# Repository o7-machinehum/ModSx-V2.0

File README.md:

ModSx-V2.0
==========

The ModSx is open open source form factor for modular synths. 

V2.0 is a redesign of V1.0 - Instead of stacking like Arduino; the modules sit side by side.
This allows for more vertical mounted components, banana plugs, vert pots etc...

It is very much in it's infancy.

PWR Board / Proto Board
----------------
/PWR.JPG)
I've rolled the power and proto board into one, it now uses a standard ATX computer PSU and everything is fused properly.

-Walker / Ryan(DOT)CJW@Gmail(DOT)com

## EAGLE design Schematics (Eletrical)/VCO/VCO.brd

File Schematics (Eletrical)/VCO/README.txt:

__  __            _     _            _    _                 
 |  \/  |          | |   (_)          | |  | |                
 | \  / | __ _  ___| |__  _ _ __   ___| |__| |_   _ _ __ ___  
 | |\/| |/ _` |/ __| '_ \| | '_ \ / _ \  __  | | | | '_ ` _ \ 
 | |  | | (_| | (__| | | | | | | |  __/ |  | | |_| | | | | | |
 |_|  |_|\__,_|\___|_| |_|_|_| |_|\___|_|  |_|\__,_|_| |_| |_|
                                                              
V0.1 - Voltage Controlled Oscillator

Based off of a cct found on page 19 of TI's "LM13700" datasheet.

http://www.ti.com/lit/ds/symlink/lm13700.pdf

To do:

-Walker

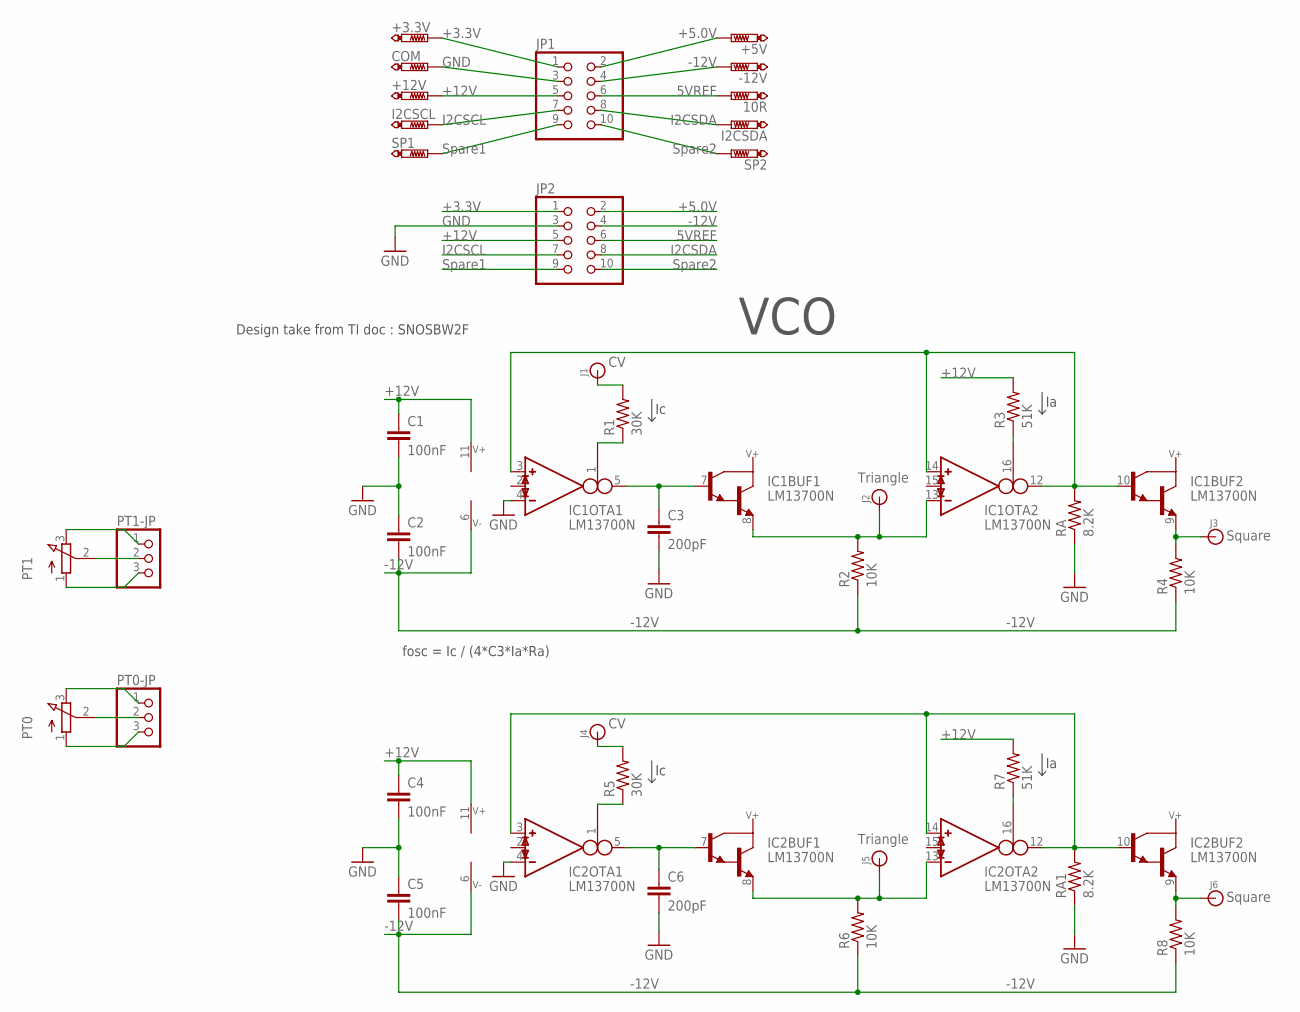
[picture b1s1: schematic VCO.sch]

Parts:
10R: PTR1B1,27; B1,27
+3.3V, +5V, +12V: PTR1B1,27; B1,27
-12V: PTR1B1,27; B1,27
C1, C2, C4, C5: 100nF; C5B2.5
C3, C6: 200pF; C5B2.5
COM: PTR1B1,27; B1,27
I2CSCL, I2CSDA: PTR1B1,27; B1,27
IC1, IC2: LM13700N; DIL16
J1, J2, J3, J4, J5, J6: BANANA_CONN
JP1, JP2: PINHD-2X5/90; 2X05/90
PT0, PT1: 3RP/1610N
PT0-JP, PT1-JP: PINHD-1X3; 1X03
R1, R5: 30K; 0207/10
R2, R4, R6, R8: 10K; 0207/10
R3, R7: 51K; 0207/10
RA, RA1: 8.2K; 0207/10
SP1, SP2: PTR1B1,27; B1,27

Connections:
5VREF: 10R.TP, JP1.6, JP2.6
+3.3V: +3.3V.TP, JP1.1, JP2.1
+5.0V: +5V.TP, JP1.2, JP2.2
+12V: +12V.TP, C1.1, C4.1, IC1.11 (V+), IC2.11 (V+), JP1.5, JP2.5, R3.2, R7.2
-12V: -12V.TP, C2.2, C5.2, IC1.6 (V-), IC2.6 (V-), JP1.4, JP2.4, R2.1, R4.1, R6.1, R8.1
CV: J1.P$1, R1.2
CV1: J4.P$1, R5.2
GND: C1.2, C2.1, C3.2, C4.2, C5.1, C6.2, COM.TP, IC1.4 (IN_N), IC2.4 (IN_N), JP1.3, JP2.3, RA.1, RA1.1
I2CSCL: I2CSCL.TP, JP1.7, JP2.7
I2CSDA: I2CSDA.TP, JP1.8, JP2.8
unnamed: C3.1, IC1.5 (OUT), IC1.7 (B)
unnamed: IC1.1 (I_BIAS), R1.1
unnamed: C6.1, IC2.5 (OUT), IC2.7 (B)
unnamed: IC1.16 (I_BIAS), R3.1
unnamed: IC2.1 (I_BIAS), R5.1
unnamed: IC1.3 (IN_P), IC1.10 (B), IC1.12 (OUT), IC1.14 (IN_P), RA.2
unnamed: IC2.3 (IN_P), IC2.10 (B), IC2.12 (OUT), IC2.14 (IN_P), RA1.2
unnamed: IC2.16 (I_BIAS), R7.1
unnamed: PT1.2 (S), PT1-JP.2
unnamed: PT1.3 (E), PT1-JP.1
unnamed: PT1.1 (A), PT1-JP.3
unnamed: PT0.2 (S), PT0-JP.2
unnamed: PT0.3 (E), PT0-JP.1
unnamed: PT0.1 (A), PT0-JP.3
SPARE1: JP1.9, JP2.9, SP1.TP
SPARE2: JP1.10, JP2.10, SP2.TP
SQ: IC1.9 (E), J3.P$1, R4.2
SQ1: IC2.9 (E), J6.P$1, R8.2
TRI: IC1.8 (E), IC1.13 (IN_N), J2.P$1, R2.2
TRI1: IC2.8 (E), IC2.13 (IN_N), J5.P$1, R6.2

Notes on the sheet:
+3.3V
GND
+12V
Spare1
+5.0V
-12V
5VREF
I2CSDA
I2CSCL
Spare2
Triangle
Square
Design take from TI doc : SNOSBW2F
VCO
fosc = Ic / (4*C3*Ia*Ra)

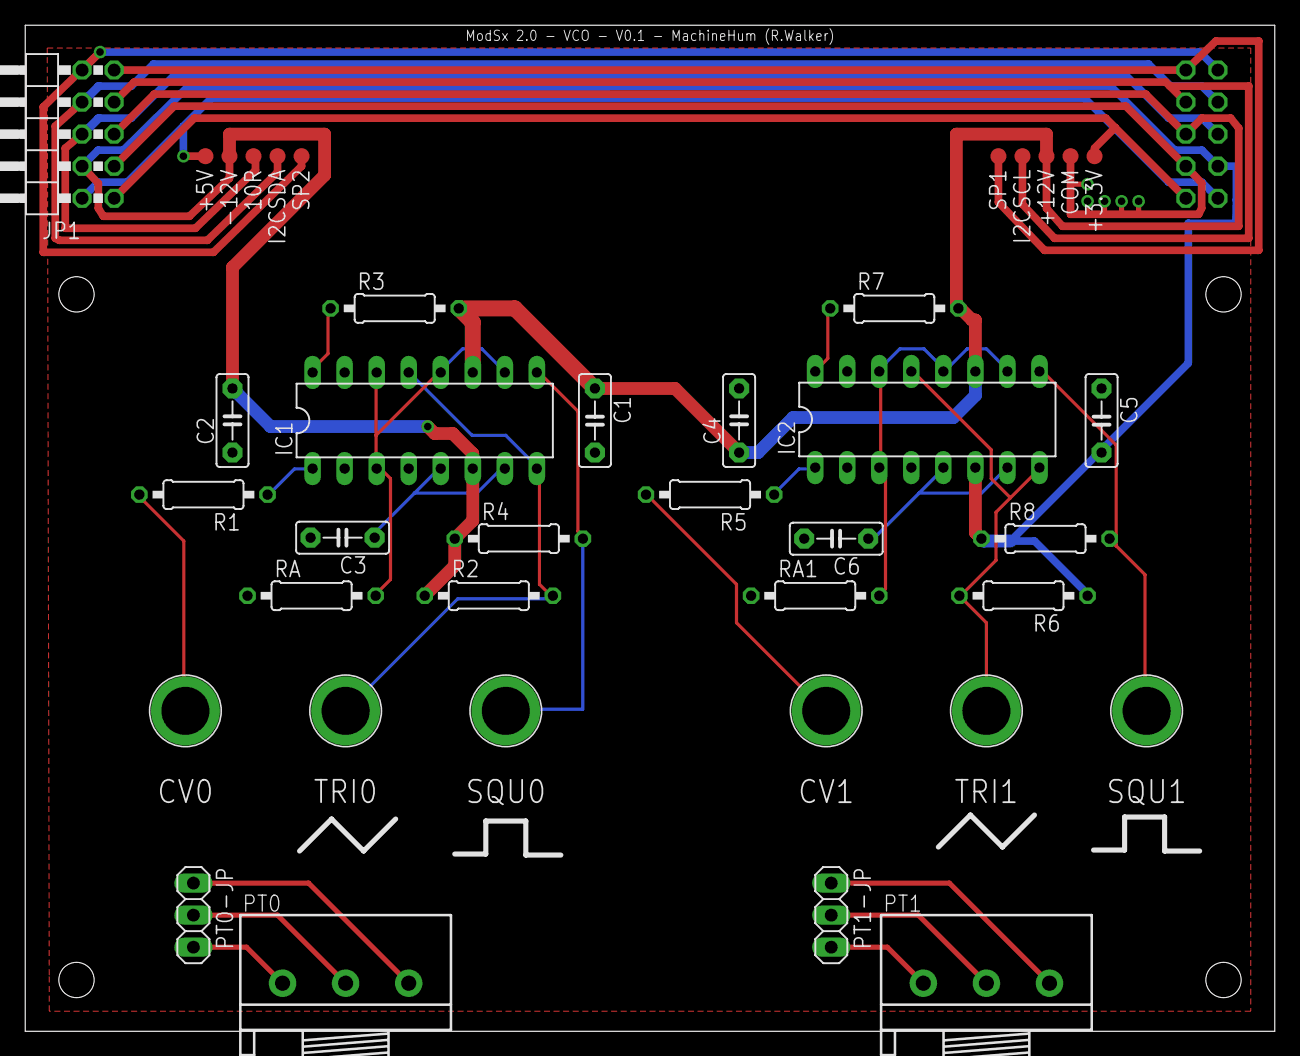
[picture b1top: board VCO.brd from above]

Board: 2 copper layers, 99.1 x 79.8 mm, 40 parts (1 on the bottom side), 30 nets.

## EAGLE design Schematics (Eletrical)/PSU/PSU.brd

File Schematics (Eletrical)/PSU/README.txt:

__  __            _     _            _    _                 
 |  \/  |          | |   (_)          | |  | |                
 | \  / | __ _  ___| |__  _ _ __   ___| |__| |_   _ _ __ ___  
 | |\/| |/ _` |/ __| '_ \| | '_ \ / _ \  __  | | | | '_ ` _ \ 
 | |  | | (_| | (__| | | | | | | |  __/ |  | | |_| | | | | | |
 |_|  |_|\__,_|\___|_| |_|_|_| |_|\___|_|  |_|\__,_|_| |_| |_|
                                                              
P0.1
Power supply & prototypeing PCB                                                              

To do:

-Walker

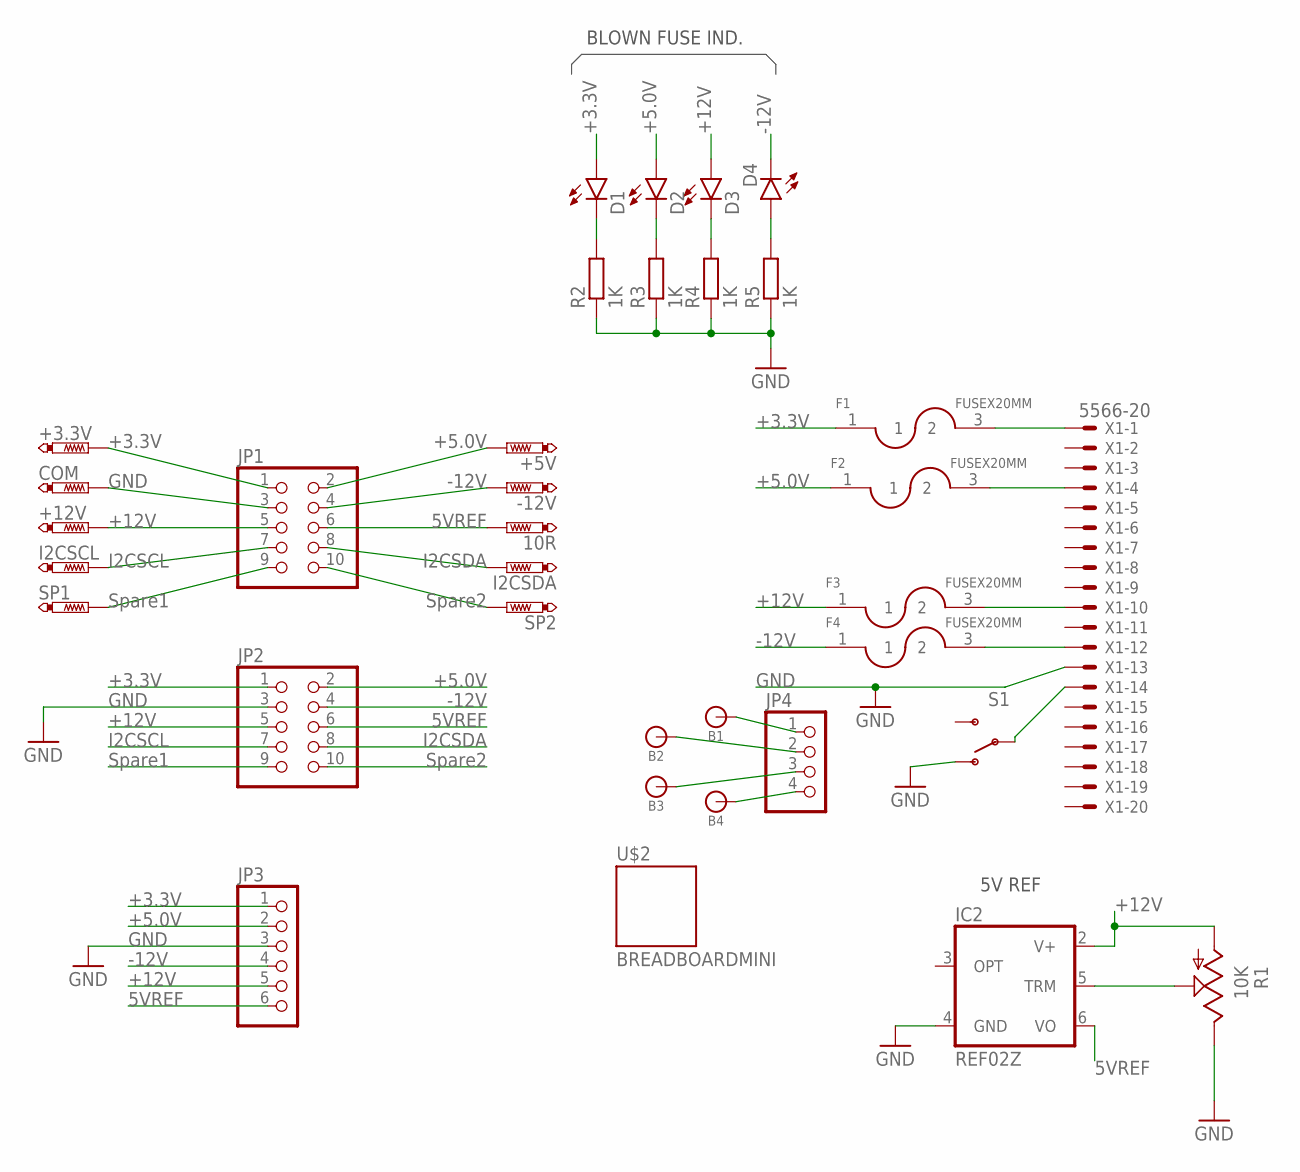
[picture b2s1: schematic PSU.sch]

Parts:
10R: PTR1B1,27; B1,27
+3.3V, +5V, +12V: PTR1B1,27; B1,27
-12V: PTR1B1,27; B1,27
B1, B2, B3, B4: BANANA_CONN
COM: PTR1B1,27; B1,27
D1, D2, D3, D4: LED5MM
F1, F2, F3, F4: FUSEX20MM; FUSE_5MM
I2CSCL, I2CSDA: PTR1B1,27; B1,27
IC2: REF02Z; DIL08
JP1, JP2: PINHD-2X5/90; 2X05/90
JP3: PINHD-1X6; 1X06
JP4: PINHD-1X4; 1X04
R1: 10K; PT-10
R2, R3, R4, R5: 1K; RTH025W
S1: SWITCH-SPDTPTH; SWITCH-SPDT
SP1, SP2: PTR1B1,27; B1,27
U$2: BREADBOARDMINI; BREADBOARD-MINI
X1: 5566-20

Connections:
5VREF: 10R.TP, IC2.6 (VO), JP1.6, JP2.6, JP3.6
+3.3V: +3.3V.TP, D1.A, F1.1, JP1.1, JP2.1, JP3.1
+5.0V: +5V.TP, D2.A, F2.1, JP1.2, JP2.2, JP3.2
+12V: +12V.TP, D3.A, F3.1, IC2.2 (V+), JP1.5, JP2.5, JP3.5, R1.A
-12V: -12V.TP, D4.K (C), F4.1, JP1.4, JP2.4, JP3.4
B1: B1.P$1, JP4.1
B2: B2.P$1, JP4.2
B3: B3.P$1, JP4.3
B4: B4.P$1, JP4.4
GND: COM.TP, IC2.4 (GND), JP1.3, JP2.3, JP3.3, R1.E, R2.1, R3.1, R4.1, R5.1, S1.1 (O), X1.13
I2CSCL: I2CSCL.TP, JP1.7, JP2.7
I2CSDA: I2CSDA.TP, JP1.8, JP2.8
unnamed: F2.3 (2), X1.4
unnamed: F3.3 (2), X1.10
unnamed: F4.3 (2), X1.12
unnamed: IC2.5 (TRM), R1.S
unnamed: F1.3 (2), X1.1
unnamed: D1.K (C), R2.2
unnamed: D2.K (C), R3.2
unnamed: D3.K (C), R4.2
unnamed: D4.A, R5.2
unnamed: S1.2, X1.14
SPARE1: JP1.9, JP2.9, SP1.TP
SPARE2: JP1.10, JP2.10, SP2.TP

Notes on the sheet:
+3.3V
GND
+12V
Spare1
+5.0V
-12V
5VREF
I2CSDA
I2CSCL
Spare2
5V REF
BLOWN FUSE IND.

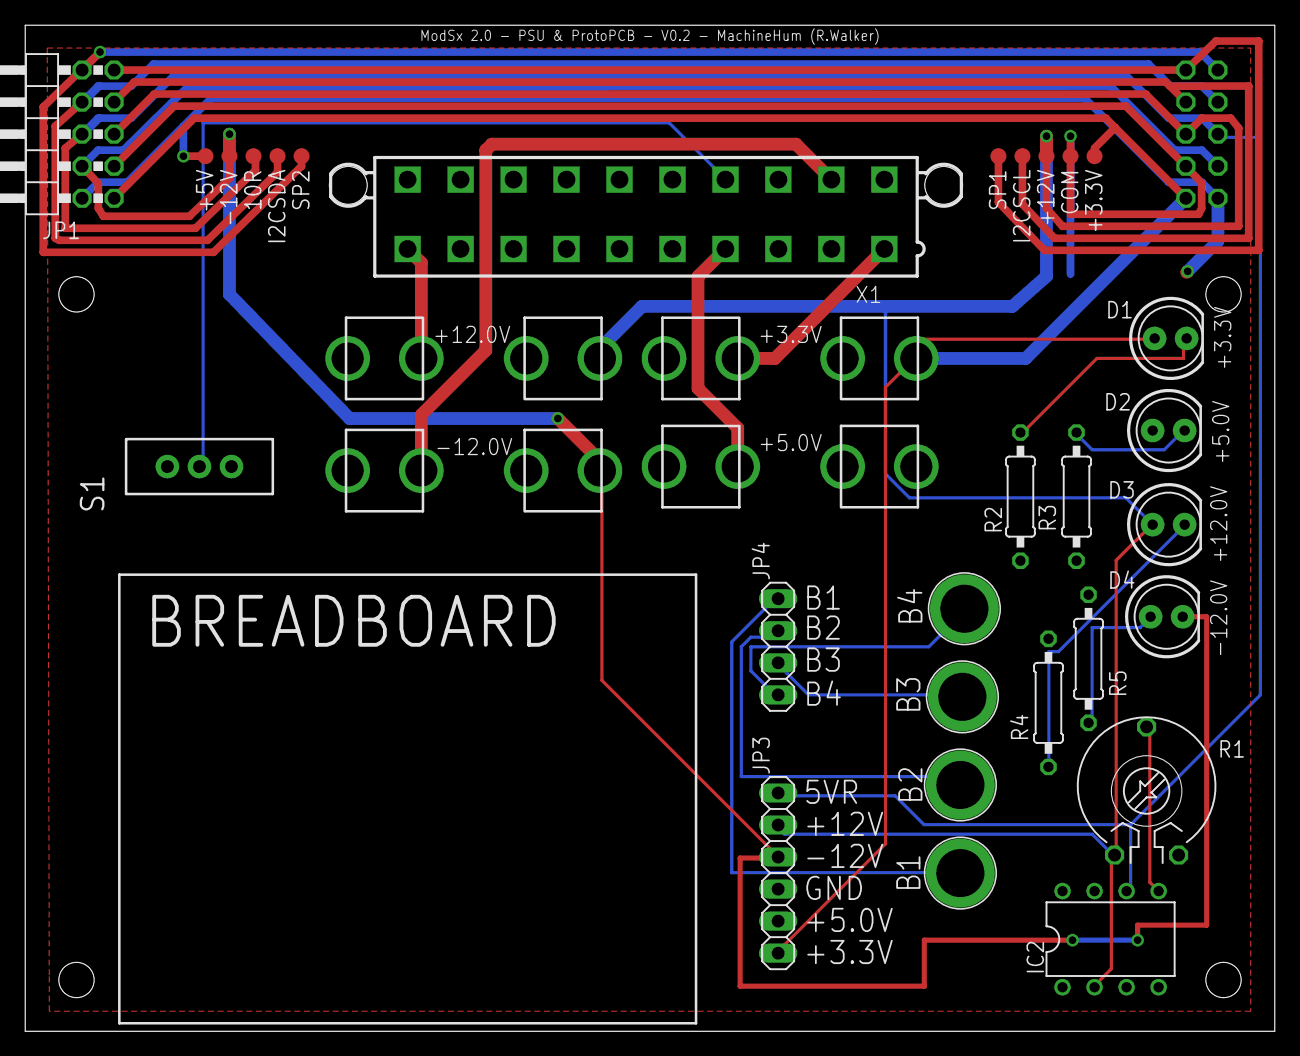
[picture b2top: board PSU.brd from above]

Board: 2 copper layers, 99.1 x 79.8 mm, 35 parts (1 on the bottom side), 24 nets.

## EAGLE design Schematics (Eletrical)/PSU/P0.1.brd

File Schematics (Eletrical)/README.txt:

__  __            _     _            _    _                 
 |  \/  |          | |   (_)          | |  | |                
 | \  / | __ _  ___| |__  _ _ __   ___| |__| |_   _ _ __ ___  
 | |\/| |/ _` |/ __| '_ \| | '_ \ / _ \  __  | | | | '_ ` _ \ 
 | |  | | (_| | (__| | | | | | | |  __/ |  | | |_| | | | | | |
 |_|  |_|\__,_|\___|_| |_|_|_| |_|\___|_|  |_|\__,_|_| |_| |_|
                                                              
V0.1

To do:

-Walker

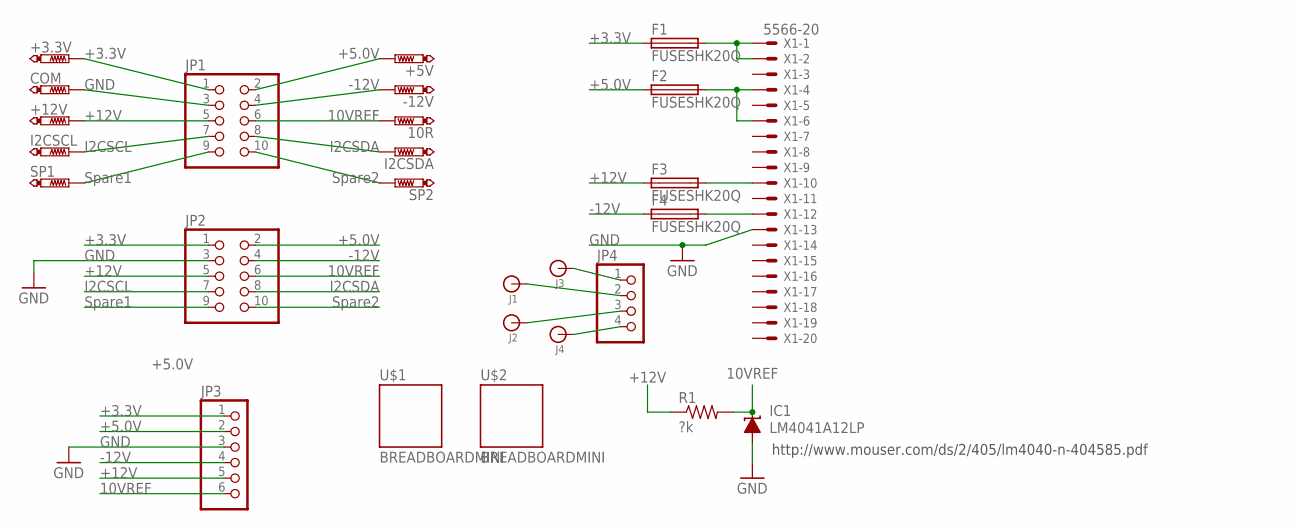
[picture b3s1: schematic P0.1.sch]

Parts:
10R: PTR1B1,27; B1,27
+3.3V, +5V, +12V: PTR1B1,27; B1,27
-12V: PTR1B1,27; B1,27
COM: PTR1B1,27; B1,27
F1, F2, F3, F4: FUSESHK20Q; SHK20Q
I2CSCL, I2CSDA: PTR1B1,27; B1,27
IC1: LM4041A12LP; LP_O-PBCY-W3
J1, J2, J3, J4: BANANA_CONN
JP1, JP2: PINHD-2X5/90; 2X05/90
JP3: PINHD-1X6; 1X06
JP4: PINHD-1X4; 1X04
R1: ?k; 0204/7
SP1, SP2: PTR1B1,27; B1,27
U$1, U$2: BREADBOARDMINI; BREADBOARD-MINI
X1: 5566-20

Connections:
10VREF: 10R.TP, IC1.2 (C), JP1.6, JP2.6, JP3.6, R1.2
+3.3V: +3.3V.TP, F1.1A (1), JP1.1, JP2.1, JP3.1
+5.0V: +5V.TP, F2.1A (1), JP1.2, JP2.2, JP3.2
+12V: +12V.TP, F3.1A (1), JP1.5, JP2.5, JP3.5, R1.1
-12V: -12V.TP, F4.1A (1), JP1.4, JP2.4, JP3.4
GND: COM.TP, IC1.3 (A), JP1.3, JP2.3, JP3.3, X1.13
I2CSCL: I2CSCL.TP, JP1.7, JP2.7
I2CSDA: I2CSDA.TP, JP1.8, JP2.8
unnamed: F2.2A (2), X1.4, X1.6
unnamed: F3.2A (2), X1.10
unnamed: F4.2A (2), X1.12
unnamed: J3.P$1, JP4.1
unnamed: F1.2A (2), X1.1, X1.2
unnamed: J1.P$1, JP4.2
unnamed: J2.P$1, JP4.3
unnamed: J4.P$1, JP4.4
SPARE1: JP1.9, JP2.9, SP1.TP
SPARE2: JP1.10, JP2.10, SP2.TP

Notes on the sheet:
+3.3V
GND
+12V
Spare1
+5.0V
-12V
10VREF
I2CSDA
I2CSCL
Spare2
http://www.mouser.com/ds/2/405/lm4040-n-404585.pdf

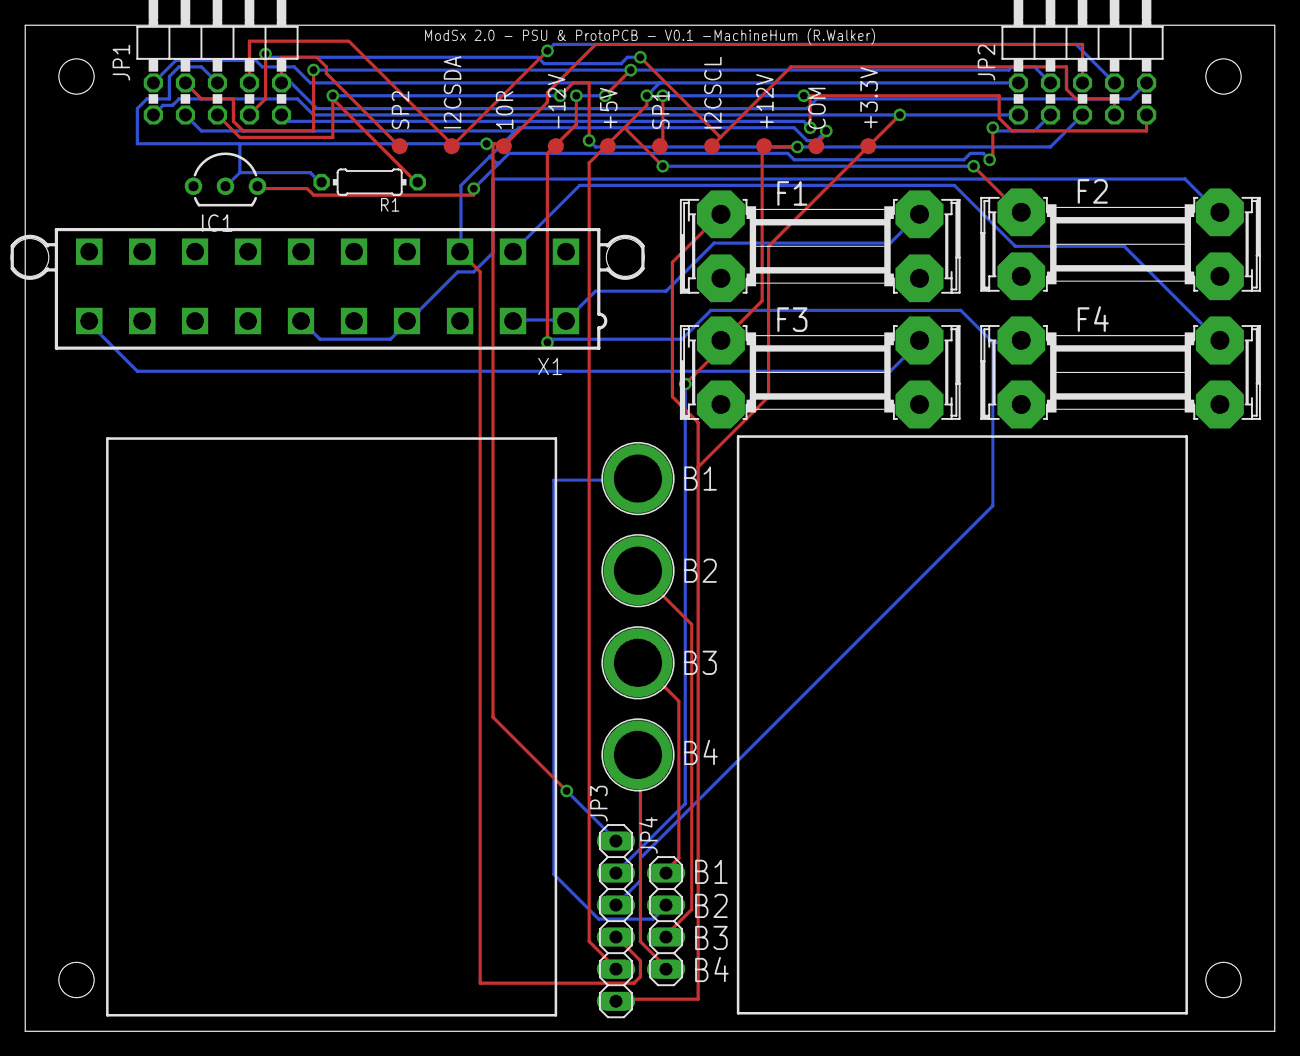
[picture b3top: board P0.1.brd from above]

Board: 2 copper layers, 99.1 x 79.8 mm, 27 parts (0 on the bottom side), 18 nets.

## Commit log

2016-02-12 Feb 11th, 2016 -------------- -First Push
2016-02-12 Feb 11th, 2016 -------------- Update
2016-02-23 Feb 22nd, 2016 -------------- -Major PCB update to PSU board -First PCBs ordered
2016-03-07 March 6th, 2016
2016-05-23 Update May/2016

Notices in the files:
parts and their libraries:
SparkFun-Connectors: Licensing: Creative Commons ShareAlike 4.0 International - https://creativecommons.org/licenses/by-sa/4.0
